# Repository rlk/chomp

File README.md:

# The Chomp

The Chomp is a clone of the Fender Champ Amp 5E1 circuit. For documentation, see http://rlk.github.io/chomp.

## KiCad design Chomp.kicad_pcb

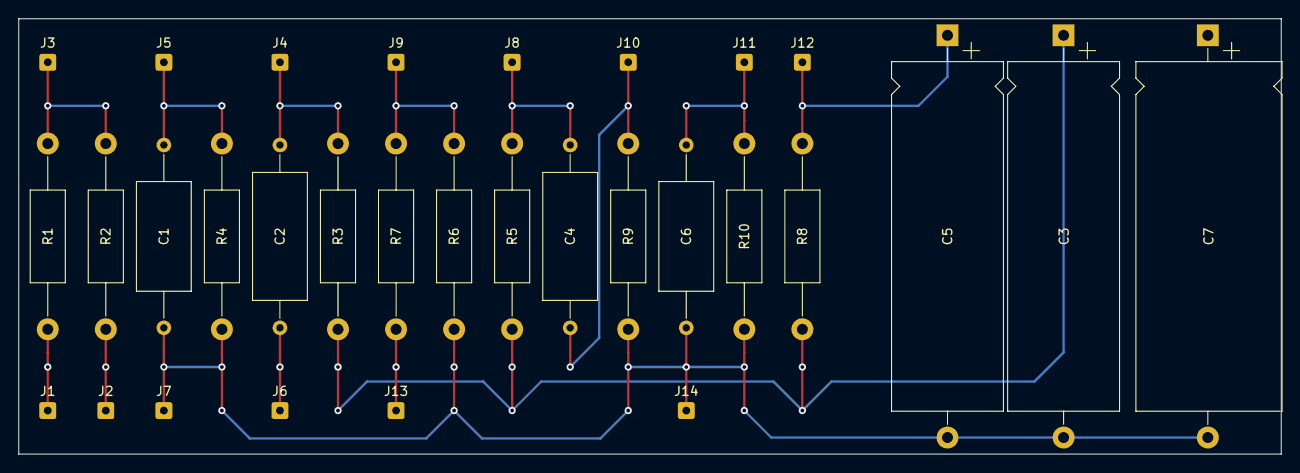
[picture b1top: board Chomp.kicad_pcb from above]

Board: 2 copper layers, 138.1 x 47.6 mm, 31 parts (0 on the bottom side), 14 nets.

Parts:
C1, C6: 25; C_Axial_L12.0mm_D6mm_P20.00mm_Horizontal
C2, C4: .022; C_Axial_L14.0mm_D6mm_P20.00mm_Horizontal
C3, C5: 10; CP_Axial_L38.0mm_D12.0mm_P44.00mm_Horizontal
C7: 15; CP_Axial_L38.0mm_D16.0mm_P44.00mm_Horizontal
J1: IN2; SolderWire-0.25sqmm_1x01_D0.65mm_OD1.7mm
J2: IN1; SolderWire-0.25sqmm_1x01_D0.65mm_OD1.7mm
J3: V1-2; SolderWire-0.25sqmm_1x01_D0.65mm_OD1.7mm
J4: V1-1; SolderWire-0.25sqmm_1x01_D0.65mm_OD1.7mm
J5: V1-3; SolderWire-0.25sqmm_1x01_D0.65mm_OD1.7mm
J6: RV1-1; SolderWire-0.25sqmm_1x01_D0.65mm_OD1.7mm
J7: RV1-3; SolderWire-0.25sqmm_1x01_D0.65mm_OD1.7mm
J8: V1-6; SolderWire-0.25sqmm_1x01_D0.65mm_OD1.7mm
J9: V1-8; SolderWire-0.25sqmm_1x01_D0.65mm_OD1.7mm
J10: V2-5; SolderWire-0.25sqmm_1x01_D0.65mm_OD1.7mm
J11: V2-8; SolderWire-0.25sqmm_1x01_D0.65mm_OD1.7mm
J12: V2-6; SolderWire-0.25sqmm_1x01_D0.65mm_OD1.7mm
J13: T2-G; SolderWire-0.25sqmm_1x01_D0.65mm_OD1.7mm
J14: T2-B; SolderWire-0.25sqmm_1x01_D0.65mm_OD1.7mm
R1, R2: 68K; R_Axial_DIN0411_L9.9mm_D3.6mm_P20.32mm_Horizontal
R3, R5: 100K; R_Axial_DIN0411_L9.9mm_D3.6mm_P20.32mm_Horizontal
R4, R6: 1K5; R_Axial_DIN0411_L9.9mm_D3.6mm_P20.32mm_Horizontal
R7, R8: 22K; R_Axial_DIN0411_L9.9mm_D3.6mm_P20.32mm_Horizontal
R9: 220K; R_Axial_DIN0411_L9.9mm_D3.6mm_P20.32mm_Horizontal
R10: 470; R_Axial_DIN0411_L9.9mm_D3.6mm_P20.32mm_Horizontal

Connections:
GND: C1.2, C3.2, C5.2, C6.2, C7.2, J7.1, J14.1, R4.2, R6.2, R9.2, R10.2
unnamed: C1.1, J5.1, R4.1
unnamed: C2.1, J4.1, R3.2
unnamed: C2.2, J6.1
unnamed: C3.1, R3.1, R5.1, R8.1
unnamed: C4.1, J8.1, R5.2
unnamed: C4.2, J10.1, R9.1
unnamed: C5.1, J12.1, R8.2
unnamed: C6.1, J11.1, R10.1
unnamed: J1.1, R1.1
unnamed: J2.1, R2.1
unnamed: J3.1, R1.2, R2.2
unnamed: J9.1, R6.1, R7.1
unnamed: J13.1, R7.2

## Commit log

2023-01-06 Fix edge cut
2023-01-16 Ground routing and layout tweaks.
    http://www.valvewizard.co.uk/Grounding.pdf gives some good advice on grounding using a Champ circuit as an example. Rather than leave the schematic ambigous on this topic, I've drawn Blencowe's recom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
2023-01-21 Update the layout diagram to reflect the final build.
2023-01-21 Add PDFs of the schematic and layout
2023-01-21 Add empty index HTML.
2023-01-21 Remove source files from gh-pages branch.
2023-01-22 Improve labeling.
2023-01-22 Update PDFs.
2023-01-26 Restructure the schematic layout to emphasize power.
2023-01-28 Update PDFs and add links.
2023-01-28 Reorient OT and add screen resistor.
2023-01-29 Convert to 5E1.
2023-02-10 Simplify choke wiring.
2023-02-10 Add text and images.
2023-02-10 Update circuit number.
2023-02-10 Update README.
2023-02-11 Fix transformer spec. Add entities.
2023-02-11 Correct plate voltage spec.
2023-02-11 Style.
